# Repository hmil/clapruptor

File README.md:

# Clapruptor version 2

Voir [explications](https://www.youtube.com/watch?v=fMc_n8CZkKc).

La version définitive du PCB est "clapruptor-2.0".

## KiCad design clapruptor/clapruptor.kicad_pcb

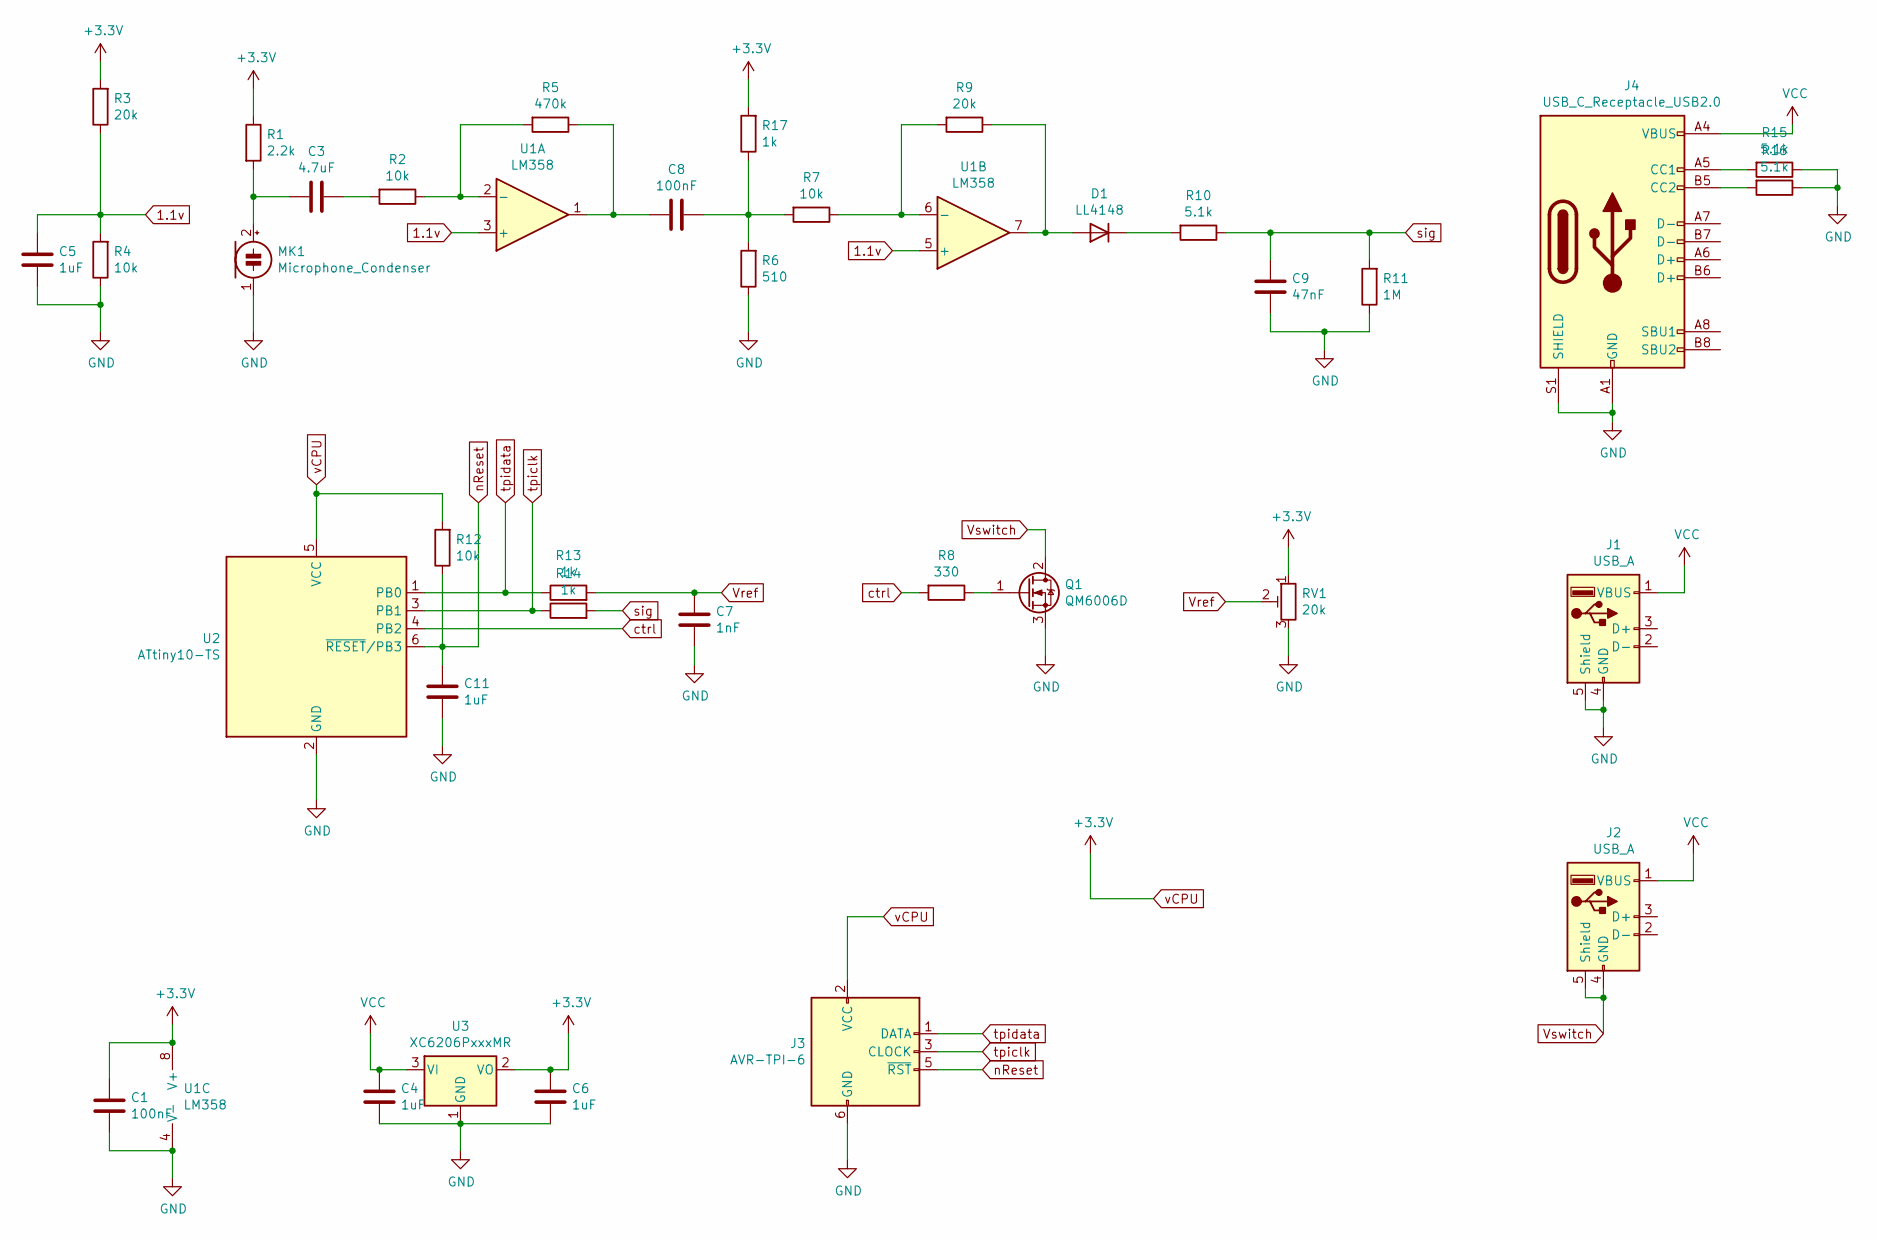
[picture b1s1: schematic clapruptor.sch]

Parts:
C1, C8: 100nF; C_0603_1608Metric_Pad1.05x0.95mm_HandSolder
C3: 4.7uF; C_0603_1608Metric_Pad1.05x0.95mm_HandSolder
C4, C5, C6, C11: 1uF; C_0603_1608Metric_Pad1.05x0.95mm_HandSolder
C7: 1nF; C_0603_1608Metric_Pad1.05x0.95mm_HandSolder
C9: 47nF; C_0603_1608Metric_Pad1.05x0.95mm_HandSolder
D1: LL4148; D_MiniMELF
J1: USB_A; USB_A_CNCTech_1001-011-01101_Horizontal
J2: USB_A; USB_A_Molex_67643_Horizontal
J3: AVR-TPI-6; Tag-Connect_TC2030-IDC-NL_2x03_P1.27mm_Vertical
J4: USB_C_Receptacle_USB2.0; USB_C_Receptacle_Palconn_UTC16-G
MK1: Microphone_Condenser; electret_microphone_10mm
Q1: QM6006D; TO-252-2
R1: 2.2k; R_0603_1608Metric_Pad1.05x0.95mm_HandSolder
R2, R4, R7, R12: 10k; R_0603_1608Metric_Pad1.05x0.95mm_HandSolder
R3, R9: 20k; R_0603_1608Metric_Pad1.05x0.95mm_HandSolder
R5: 470k; R_0603_1608Metric_Pad1.05x0.95mm_HandSolder
R6: 510; R_0603_1608Metric_Pad1.05x0.95mm_HandSolder
R8: 330; R_0603_1608Metric_Pad1.05x0.95mm_HandSolder
R10, R15, R16: 5.1k; R_0603_1608Metric_Pad1.05x0.95mm_HandSolder
R11: 1M; R_0603_1608Metric_Pad1.05x0.95mm_HandSolder
R13, R14, R17: 1k; R_0603_1608Metric_Pad1.05x0.95mm_HandSolder
RV1: 20k; Potentiometer_Runtron_RM-065_Vertical
U1: LM358; SOIC-8_3.9x4.9mm_P1.27mm
U2: ATtiny10-TS; SOT-23-6
U3: XC6206PxxxMR; SOT-23

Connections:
1.1v: C5.2, R3.1, R4.2, U1.3 (+), U1.5 (+)
GND: C1.2, C4.2, C5.1, C6.2, C7.1, C9.1, C11.2, J1.4 (GND), J1.5 (Shield), J3.6 (GND), J4.A1 (GND), J4.A12 (GND), J4.B1 (GND), J4.B12 (GND), J4.S1 (SHIELD), MK1.1 (-), Q1.3 (S), R4.1, R6.1, R11.1, R15.1, R16.1, RV1.3, U1.4 (V-), U2.2 (GND), U3.1 (GND)
unnamed: C3.1, R2.2
unnamed: C3.2, MK1.2 (+), R1.2
unnamed: C8.1, R6.2, R7.2, R17.1
unnamed: C8.2, R5.1, U1.1
unnamed: D1.1 (K), R10.2
unnamed: D1.2 (A), R9.1, U1.7
unnamed: J4.A5 (CC1), R15.2
unnamed: J4.B5 (CC2), R16.2
unnamed: Q1.1 (G), R8.1
unnamed: R2.1, R5.2, U1.2 (-)
unnamed: R7.1, R9.2, U1.6 (-)
VCC: C4.1, J1.1 (VBUS), J2.1 (VBUS), J4.A4 (VBUS), J4.A9 (VBUS), J4.B4 (VBUS), J4.B9 (VBUS), U3.3 (VI)
Vref: C7.2, R13.2, RV1.2
Vswitch: J2.4 (GND), J2.5 (Shield), Q1.2 (D)
ctrl: R8.2, U2.4 (PB2)
nReset: C11.1, J3.5 (~RST), R12.1, U2.6 (~RESET~/PB3)
sig: C9.2, R10.1, R11.2, R14.2
tpiclk: J3.3 (CLOCK), R14.1, U2.3 (PB1)
tpidata: J3.1 (DATA), R13.1, U2.1 (PB0)
vCPU: C1.1, C6.1, J3.2 (VCC), R1.1, R3.2, R12.2, R17.2, RV1.1, U1.8 (V+), U2.5 (VCC), U3.2 (VO)

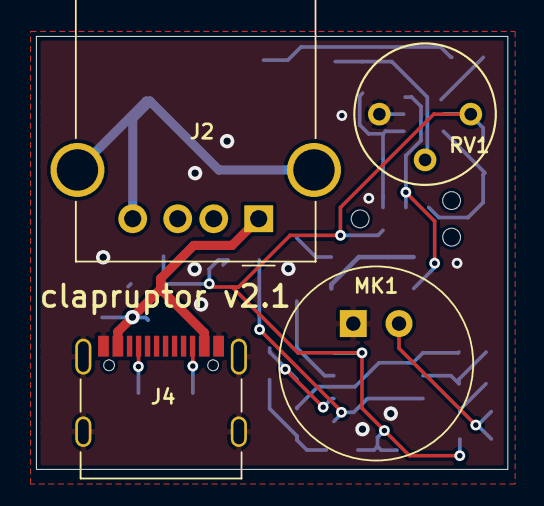
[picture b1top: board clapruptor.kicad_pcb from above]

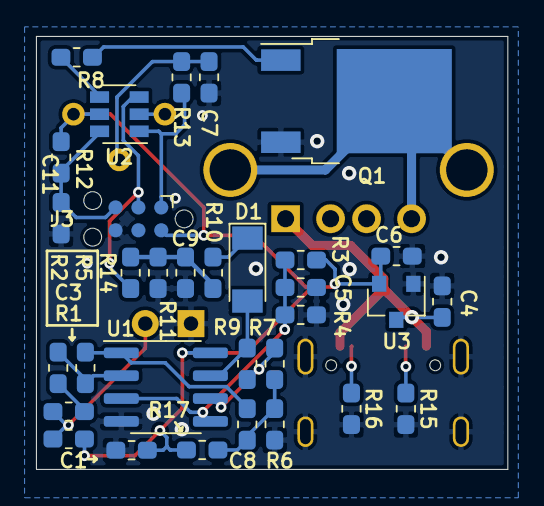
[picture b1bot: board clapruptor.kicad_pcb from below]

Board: 2 copper layers, 26.2 x 24.1 mm, 36 parts (32 on the bottom side), 22 nets.
